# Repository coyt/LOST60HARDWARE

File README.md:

# LOST60HARDWARE
Hardware design files for LOST60 Bluetooth Mechanical Keyboard

#### LOST60 PCB Version 2.0 (SPRING 2020)

#### LOST60 PCB Version 1.0 (FALL 2019)

*The Ultimate Hackable Bluetooth Mechanical Keyboard*

#### Overview

Hardware design files for the LOST60 Bluetooth 60% Mechanical Keyboard PCB. The PCB utilizes a Nordic Semiconductor [nrf52840 bluetooth SoC](https://www.nordicsemi.com/?sc_itemid=%7B2DC10BA5-A76E-40F8-836E-E2FC65803A71%7D) (Rigado BMD-340 module) as the sole processor.

#### PCB Artwork

#### 3D Modeling

#### Version 2.0 System Diagram

#### Hardware Features
* 60% Mechanical Keyboard design based on GH60 Layout
* USBC connector
* Bluetooth 5.0 support
* Full RGB underlighting with "neopixels"
* Independently addressable single color key backlingting
* Qi wireless charging
* Advanced battery charging and management circuitry
* Rotary encoder and TWO speakers for Synthesizer features (under development)
* Several expansion ports (QUIIC, GROVE, CUSTOM)

#### Planned Hardware Updates

- [x] Add coulomb counting IC / improve voltage and power measurement   (Complete in V2.0)
- [ ] Improve backlighting LED brightness 
- [x] Extend USB C connector out a bit                                  (Complete in V2.0)
- [x] Fix underlighting load switch fly wire                            (Complete in V2.0)
- [x] Fix LiPo charger ground pour problem & improve charge rate        (Complete in V2.0)
- [x] Remove onboard Lithium protection IC                              (Complete in V2.0)
- [ ] Add physical power switch connection point 
- [ ] Change wiring so I/O emulates Feather nrf52840 board
- [x] Add QSPI memory chip                                              (Complete in V2.0)

#### Development Setup

This design was created using Eagle PCB for schematic capture and PCB layout and routing. Fusion 360 was used to generate CAD model of board before manufacture.

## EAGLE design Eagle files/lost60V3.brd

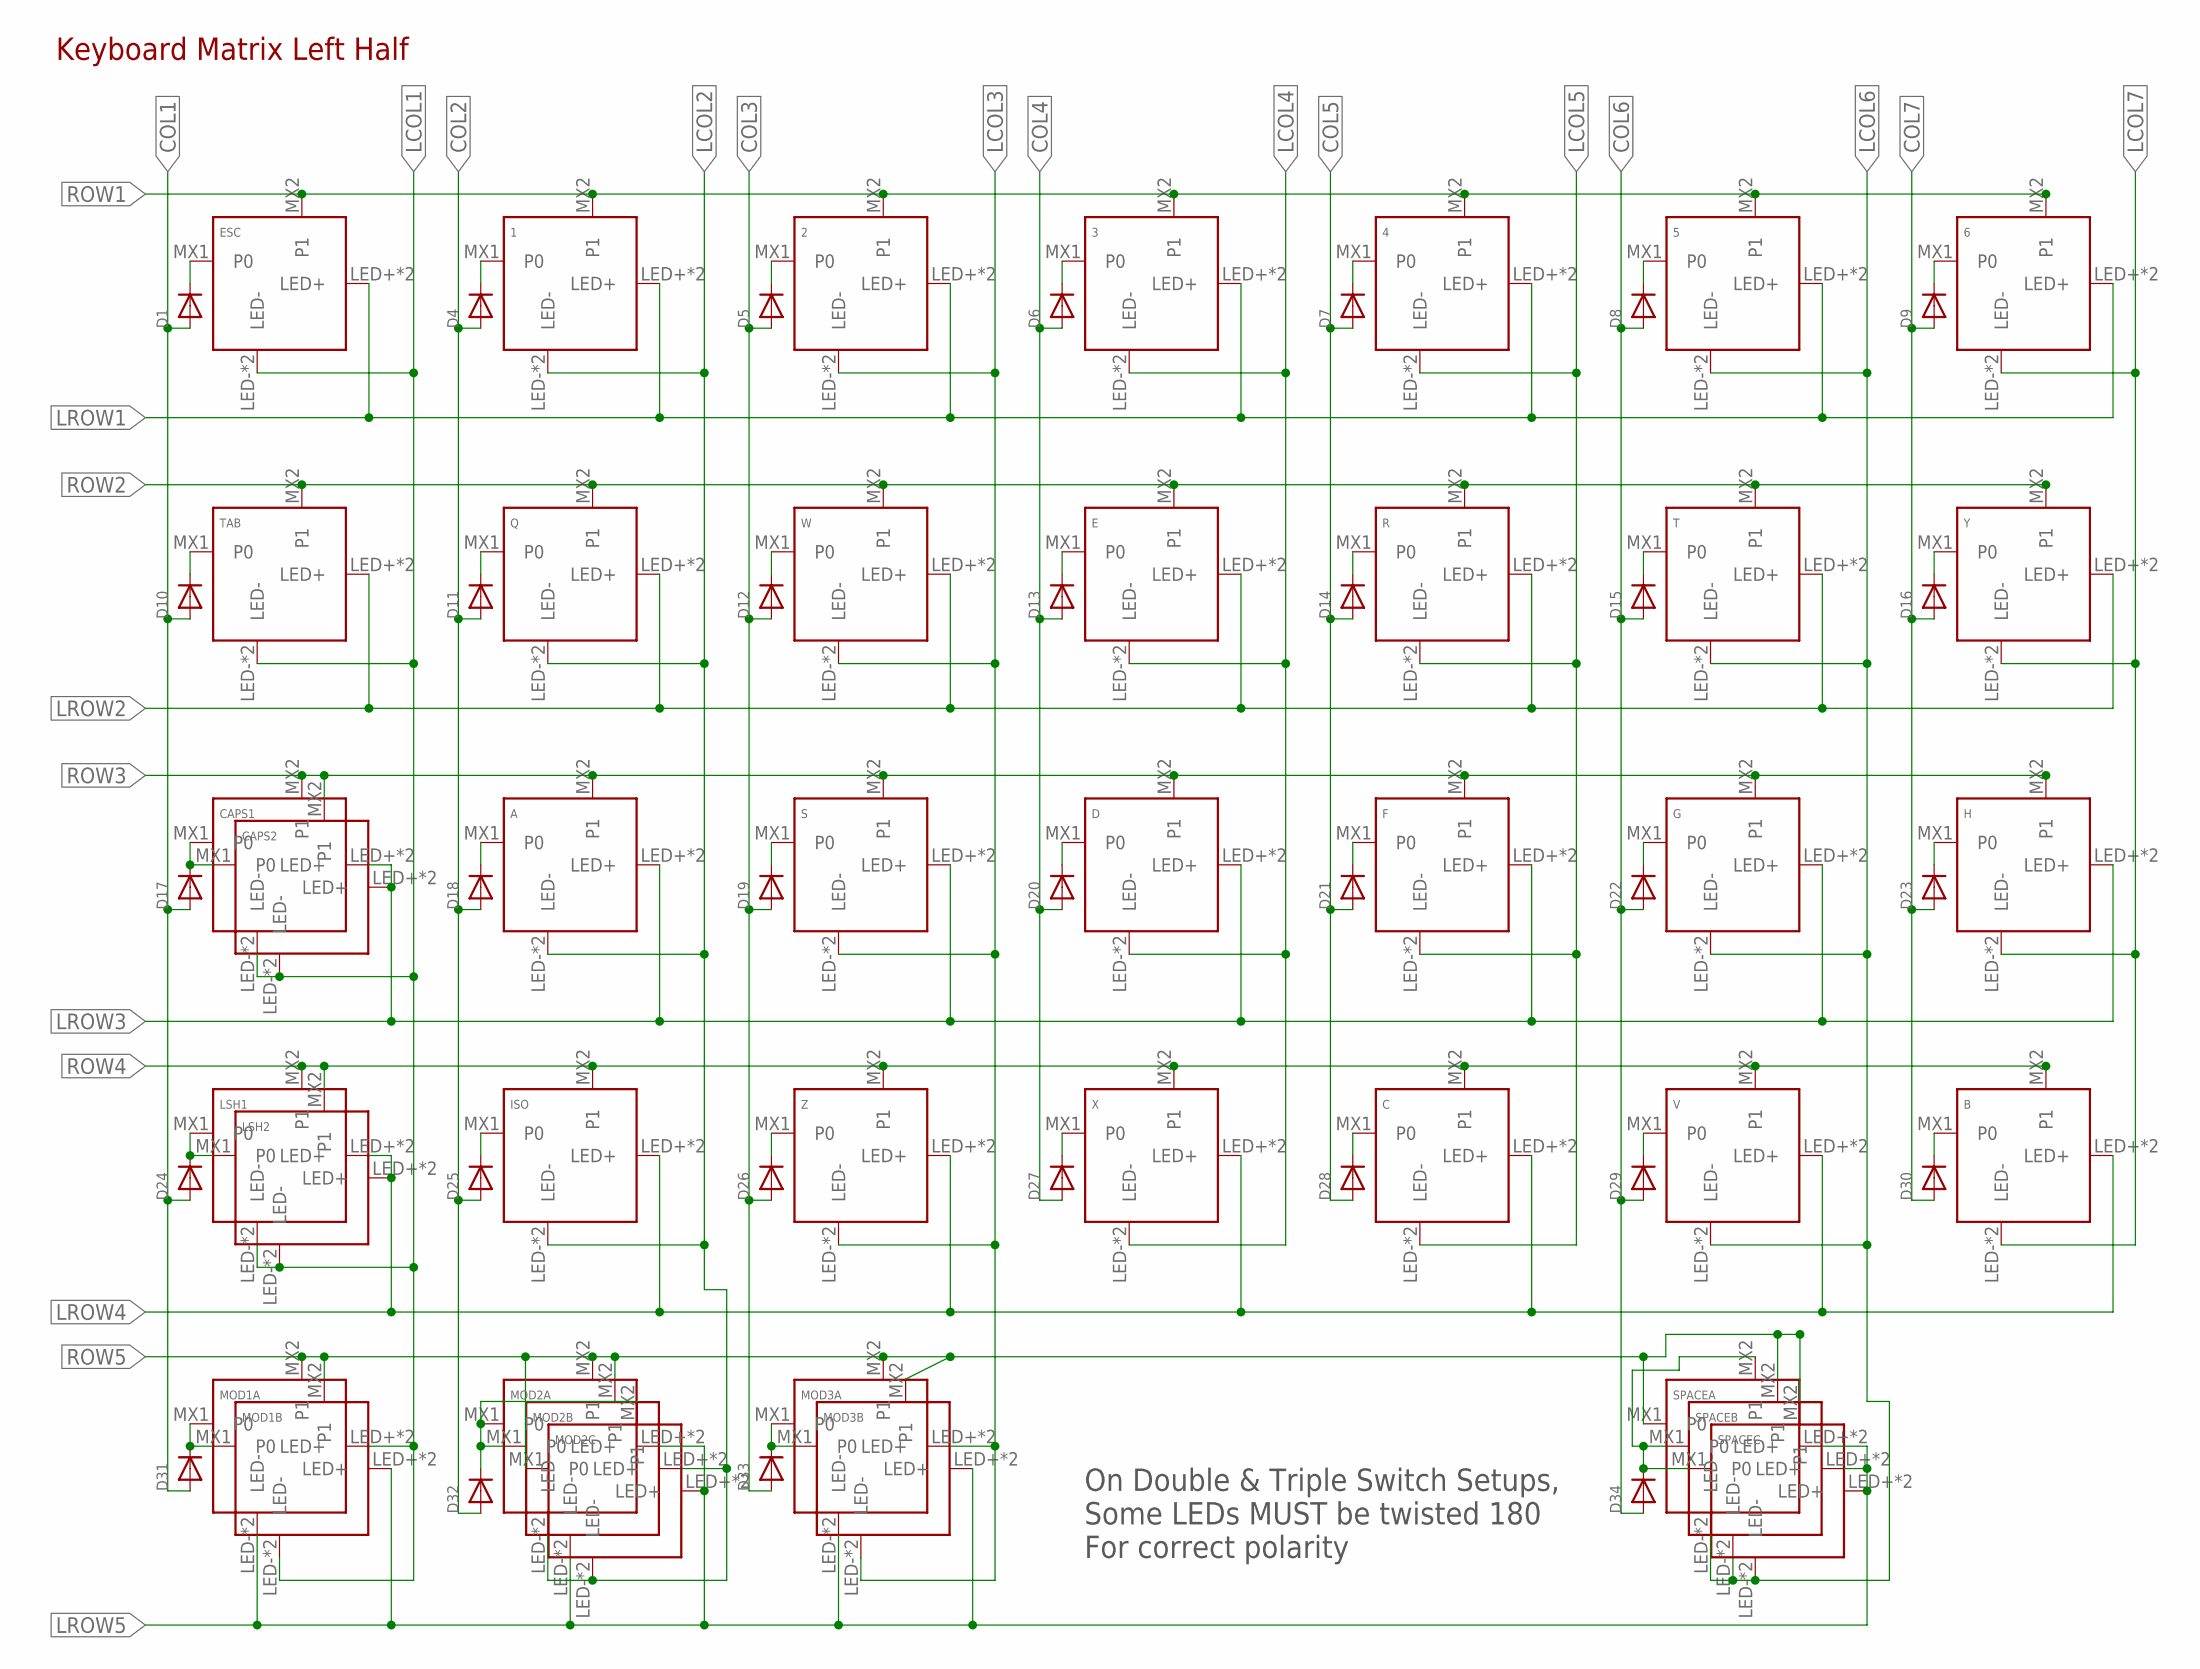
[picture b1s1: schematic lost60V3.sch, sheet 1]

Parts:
1, 2, 3, 4, 5, 6: KEYSWITCH-THTSMDLED-MX-1U-THTSMDLED; MX-1U-THTSMDLED
A: KEYSWITCH-THTSMDLED-MX-1U-THTSMDLED; MX-1U-THTSMDLED
B: KEYSWITCH-THTSMDLED-MX-1U-THTSMDLED; MX-1U-THTSMDLED
C: KEYSWITCH-THTSMDLED-MX-1U-THTSMDLED; MX-1U-THTSMDLED
CAPS1, CAPS2: KEYSWITCH-THTSMDLED-MX-1U-THTSMDLED; MX-1U-THTSMDLED
D: KEYSWITCH-THTSMDLED-MX-1U-THTSMDLED; MX-1U-THTSMDLED
D1, D4, D5, D6, D7, D8, D9, D10, D11, D12, D13, D14, D15, D16, D17, D18, D19, D20, D21, D22, D23, D24, D25, D26, D27, D28, D29, D30, D31, D32, D33, D34: DIODESOD-523; SOD-523
E: KEYSWITCH-THTSMDLED-MX-1U-THTSMDLED; MX-1U-THTSMDLED
ESC: KEYSWITCH-THTSMDLED-MX-1U-THTSMDLED; MX-1U-THTSMDLED
F: KEYSWITCH-THTSMDLED-MX-1U-THTSMDLED; MX-1U-THTSMDLED
G: KEYSWITCH-THTSMDLED-MX-1U-THTSMDLED; MX-1U-THTSMDLED
H: KEYSWITCH-THTSMDLED-MX-1U-THTSMDLED; MX-1U-THTSMDLED
ISO: KEYSWITCH-THTSMDLED-MX-1U-THTSMDLED; MX-1U-THTSMDLED
LSH1: KEYSWITCH-THTSMDLED-MX-1U-THTSMDLED; MX-1U-THTSMDLED
LSH2: KEYSWITCH-THTSMDLED-MX-2U-THTSMDLED; MX-2U-THTSMDLED
MOD1A, MOD1B, MOD2A, MOD2B, MOD2C, MOD3A, MOD3B: KEYSWITCH-THTSMDLED-MX-1U-THTSMDLED; MX-1U-THTSMDLED
Q: KEYSWITCH-THTSMDLED-MX-1U-THTSMDLED; MX-1U-THTSMDLED
R: KEYSWITCH-THTSMDLED-MX-1U-THTSMDLED; MX-1U-THTSMDLED
S: KEYSWITCH-THTSMDLED-MX-1U-THTSMDLED; MX-1U-THTSMDLED
SPACEA: KEYSWITCH-THTSMDLED-MX-6.25U-THTSMDLED-FLIPPED; MX-6.25U-THTSMDLED-FLIPPED
SPACEB: KEYSWITCH-THTSMDLED-MX-7U-THTSMDLED-FLIPPED; MX-7U-THTSMDLED-FLIPPED
SPACEC: KEYSWITCH-THTSMDLED-MX-7U-THTSMDLED-FLIPPED; MX-7U-THTSMDLED-FLIPPED
T: KEYSWITCH-THTSMDLED-MX-1U-THTSMDLED; MX-1U-THTSMDLED
TAB: KEYSWITCH-THTSMDLED-MX-1U-THTSMDLED; MX-1U-THTSMDLED
V: KEYSWITCH-THTSMDLED-MX-1U-THTSMDLED; MX-1U-THTSMDLED
W: KEYSWITCH-THTSMDLED-MX-1U-THTSMDLED; MX-1U-THTSMDLED
X: KEYSWITCH-THTSMDLED-MX-1U-THTSMDLED; MX-1U-THTSMDLED
Y: KEYSWITCH-THTSMDLED-MX-1U-THTSMDLED; MX-1U-THTSMDLED
Z: KEYSWITCH-THTSMDLED-MX-1U-THTSMDLED; MX-1U-THTSMDLED

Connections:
COL1: D1.A, D10.A, D17.A, D24.A, D31.A; also elsewhere on the board
COL2: D4.A, D11.A, D18.A, D25.A, D32.A; also elsewhere on the board
COL3: D5.A, D12.A, D19.A, D26.A, D33.A; also elsewhere on the board
COL4: D6.A, D13.A, D20.A, D27.A; also elsewhere on the board
COL5: D7.A, D14.A, D21.A, D28.A; also elsewhere on the board
COL6: D8.A, D15.A, D22.A, D29.A, D34.A; also elsewhere on the board
COL7: D9.A, D16.A, D23.A, D30.A; also elsewhere on the board
LCOL1: CAPS1.LED-, CAPS1.SMDLED- (LED-), CAPS2.LED-, CAPS2.SMDLED- (LED-), ESC.LED-, ESC.SMDLED- (LED-), LSH1.LED-, LSH1.SMDLED- (LED-), LSH2.LED-, LSH2.SMDLED- (LED-), MOD1A.LED+, MOD1A.SMDLED+ (LED+), MOD1B.LED-, MOD1B.SMDLED- (LED-), TAB.LED-, TAB.SMDLED- (LED-); also elsewhere on the board
LCOL2: 1.LED-, 1.SMDLED- (LED-), A.LED-, A.SMDLED- (LED-), ISO.LED-, ISO.SMDLED- (LED-), MOD2A.LED-, MOD2A.SMDLED- (LED-), MOD2B.LED+, MOD2B.SMDLED+ (LED+), MOD2C.LED-, MOD2C.SMDLED- (LED-), Q.LED-, Q.SMDLED- (LED-); also elsewhere on the board
LCOL3: 2.LED-, 2.SMDLED- (LED-), MOD3A.LED+, MOD3A.SMDLED+ (LED+), MOD3B.LED-, MOD3B.SMDLED- (LED-), S.LED-, S.SMDLED- (LED-), W.LED-, W.SMDLED- (LED-), Z.LED-, Z.SMDLED- (LED-); also elsewhere on the board
LCOL4: 3.LED-, 3.SMDLED- (LED-), D.LED-, D.SMDLED- (LED-), E.LED-, E.SMDLED- (LED-), X.LED-, X.SMDLED- (LED-); also elsewhere on the board
LCOL5: 4.LED-, 4.SMDLED- (LED-), C.LED-, C.SMDLED- (LED-), F.LED-, F.SMDLED- (LED-), R.LED-, R.SMDLED- (LED-); also elsewhere on the board
LCOL6: 5.LED-, 5.SMDLED- (LED-), G.LED-, G.SMDLED- (LED-), SPACEA.LED-, SPACEA.SMDLED- (LED-), SPACEB.LED-, SPACEB.SMDLED- (LED-), SPACEC.LED-, SPACEC.SMDLED- (LED-), T.LED-, T.SMDLED- (LED-), V.LED-, V.SMDLED- (LED-); also elsewhere on the board
LCOL7: 6.LED-, 6.SMDLED- (LED-), B.LED-, B.SMDLED- (LED-), H.LED-, H.SMDLED- (LED-), Y.LED-, Y.SMDLED- (LED-); also elsewhere on the board
LROW1: 1.LED+, 1.SMDLED+ (LED+), 2.LED+, 2.SMDLED+ (LED+), 3.LED+, 3.SMDLED+ (LED+), 4.LED+, 4.SMDLED+ (LED+), 5.LED+, 5.SMDLED+ (LED+), 6.LED+, 6.SMDLED+ (LED+), ESC.LED+, ESC.SMDLED+ (LED+); also elsewhere on the board
LROW2: E.LED+, E.SMDLED+ (LED+), Q.LED+, Q.SMDLED+ (LED+), R.LED+, R.SMDLED+ (LED+), T.LED+, T.SMDLED+ (LED+), TAB.LED+, TAB.SMDLED+ (LED+), W.LED+, W.SMDLED+ (LED+), Y.LED+, Y.SMDLED+ (LED+); also elsewhere on the board
LROW3: A.LED+, A.SMDLED+ (LED+), CAPS1.LED+, CAPS1.SMDLED+ (LED+), CAPS2.LED+, CAPS2.SMDLED+ (LED+), D.LED+, D.SMDLED+ (LED+), F.LED+, F.SMDLED+ (LED+), G.LED+, G.SMDLED+ (LED+), H.LED+, H.SMDLED+ (LED+), S.LED+, S.SMDLED+ (LED+); also elsewhere on the board
LROW4: B.LED+, B.SMDLED+ (LED+), C.LED+, C.SMDLED+ (LED+), ISO.LED+, ISO.SMDLED+ (LED+), LSH1.LED+, LSH1.SMDLED+ (LED+), LSH2.LED+, LSH2.SMDLED+ (LED+), V.LED+, V.SMDLED+ (LED+), X.LED+, X.SMDLED+ (LED+), Z.LED+, Z.SMDLED+ (LED+); also elsewhere on the board
LROW5: MOD1A.LED-, MOD1A.SMDLED- (LED-), MOD1B.LED+, MOD1B.SMDLED+ (LED+), MOD2A.LED+, MOD2A.SMDLED+ (LED+), MOD2B.LED-, MOD2B.SMDLED- (LED-), MOD2C.LED+, MOD2C.SMDLED+ (LED+), MOD3A.LED-, MOD3A.SMDLED- (LED-), MOD3B.LED+, MOD3B.SMDLED+ (LED+), SPACEA.LED+, SPACEA.SMDLED+ (LED+), SPACEB.LED+, SPACEB.SMDLED+ (LED+), SPACEC.LED+, SPACEC.SMDLED+ (LED+); also elsewhere on the board
unnamed: D1.K (C), ESC.MX1 (P0)
unnamed: 1.MX1 (P0), D4.K (C)
unnamed: 2.MX1 (P0), D5.K (C)
unnamed: 3.MX1 (P0), D6.K (C)
unnamed: 4.MX1 (P0), D7.K (C)
unnamed: 5.MX1 (P0), D8.K (C)
unnamed: 6.MX1 (P0), D9.K (C)
unnamed: D10.K (C), TAB.MX1 (P0)
unnamed: D11.K (C), Q.MX1 (P0)
unnamed: D12.K (C), W.MX1 (P0)
unnamed: D13.K (C), E.MX1 (P0)
unnamed: D14.K (C), R.MX1 (P0)
unnamed: D15.K (C), T.MX1 (P0)
unnamed: D16.K (C), Y.MX1 (P0)
unnamed: D34.K (C), SPACEA.MX2 (P1), SPACEB.MX1 (P0), SPACEC.MX1 (P0)
unnamed: CAPS1.MX1 (P0), CAPS2.MX1 (P0), D17.K (C)
unnamed: A.MX1 (P0), D18.K (C)
unnamed: D19.K (C), S.MX1 (P0)
unnamed: D.MX1 (P0), D20.K (C)
unnamed: D21.K (C), F.MX1 (P0)
unnamed: D23.K (C), H.MX1 (P0)
unnamed: D24.K (C), LSH1.MX1 (P0), LSH2.MX1 (P0)
unnamed: D25.K (C), ISO.MX1 (P0)
unnamed: D26.K (C), Z.MX1 (P0)
unnamed: D27.K (C), X.MX1 (P0)
unnamed: C.MX1 (P0), D28.K (C)
unnamed: D29.K (C), V.MX1 (P0)
unnamed: B.MX1 (P0), D30.K (C)
unnamed: D31.K (C), MOD1A.MX1 (P0), MOD1B.MX1 (P0)
unnamed: D32.K (C), MOD2A.MX1 (P0), MOD2B.MX1 (P0), MOD2C.MX2 (P1)
unnamed: D33.K (C), MOD3A.MX1 (P0), MOD3B.MX1 (P0)
unnamed: D22.K (C), G.MX1 (P0)
ROW1: 1.MX2 (P1), 2.MX2 (P1), 3.MX2 (P1), 4.MX2 (P1), 5.MX2 (P1), 6.MX2 (P1), ESC.MX2 (P1); also elsewhere on the board
ROW2: E.MX2 (P1), Q.MX2 (P1), R.MX2 (P1), T.MX2 (P1), TAB.MX2 (P1), W.MX2 (P1), Y.MX2 (P1); also elsewhere on the board
ROW3: A.MX2 (P1), CAPS1.MX2 (P1), CAPS2.MX2 (P1), D.MX2 (P1), F.MX2 (P1), G.MX2 (P1), H.MX2 (P1), S.MX2 (P1); also elsewhere on the board
ROW4: B.MX2 (P1), C.MX2 (P1), ISO.MX2 (P1), LSH1.MX2 (P1), LSH2.MX2 (P1), V.MX2 (P1), X.MX2 (P1), Z.MX2 (P1); also elsewhere on the board
ROW5: MOD1A.MX2 (P1), MOD1B.MX2 (P1), MOD2A.MX2 (P1), MOD2B.MX2 (P1), MOD2C.MX1 (P0), MOD3A.MX2 (P1), MOD3B.MX2 (P1), SPACEA.MX1 (P0), SPACEB.MX2 (P1), SPACEC.MX2 (P1); also elsewhere on the board

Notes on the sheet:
Keyboard Matrix Left Half
On Double & Triple Switch Setups, Some LEDs MUST be twisted 180 For correct polarity

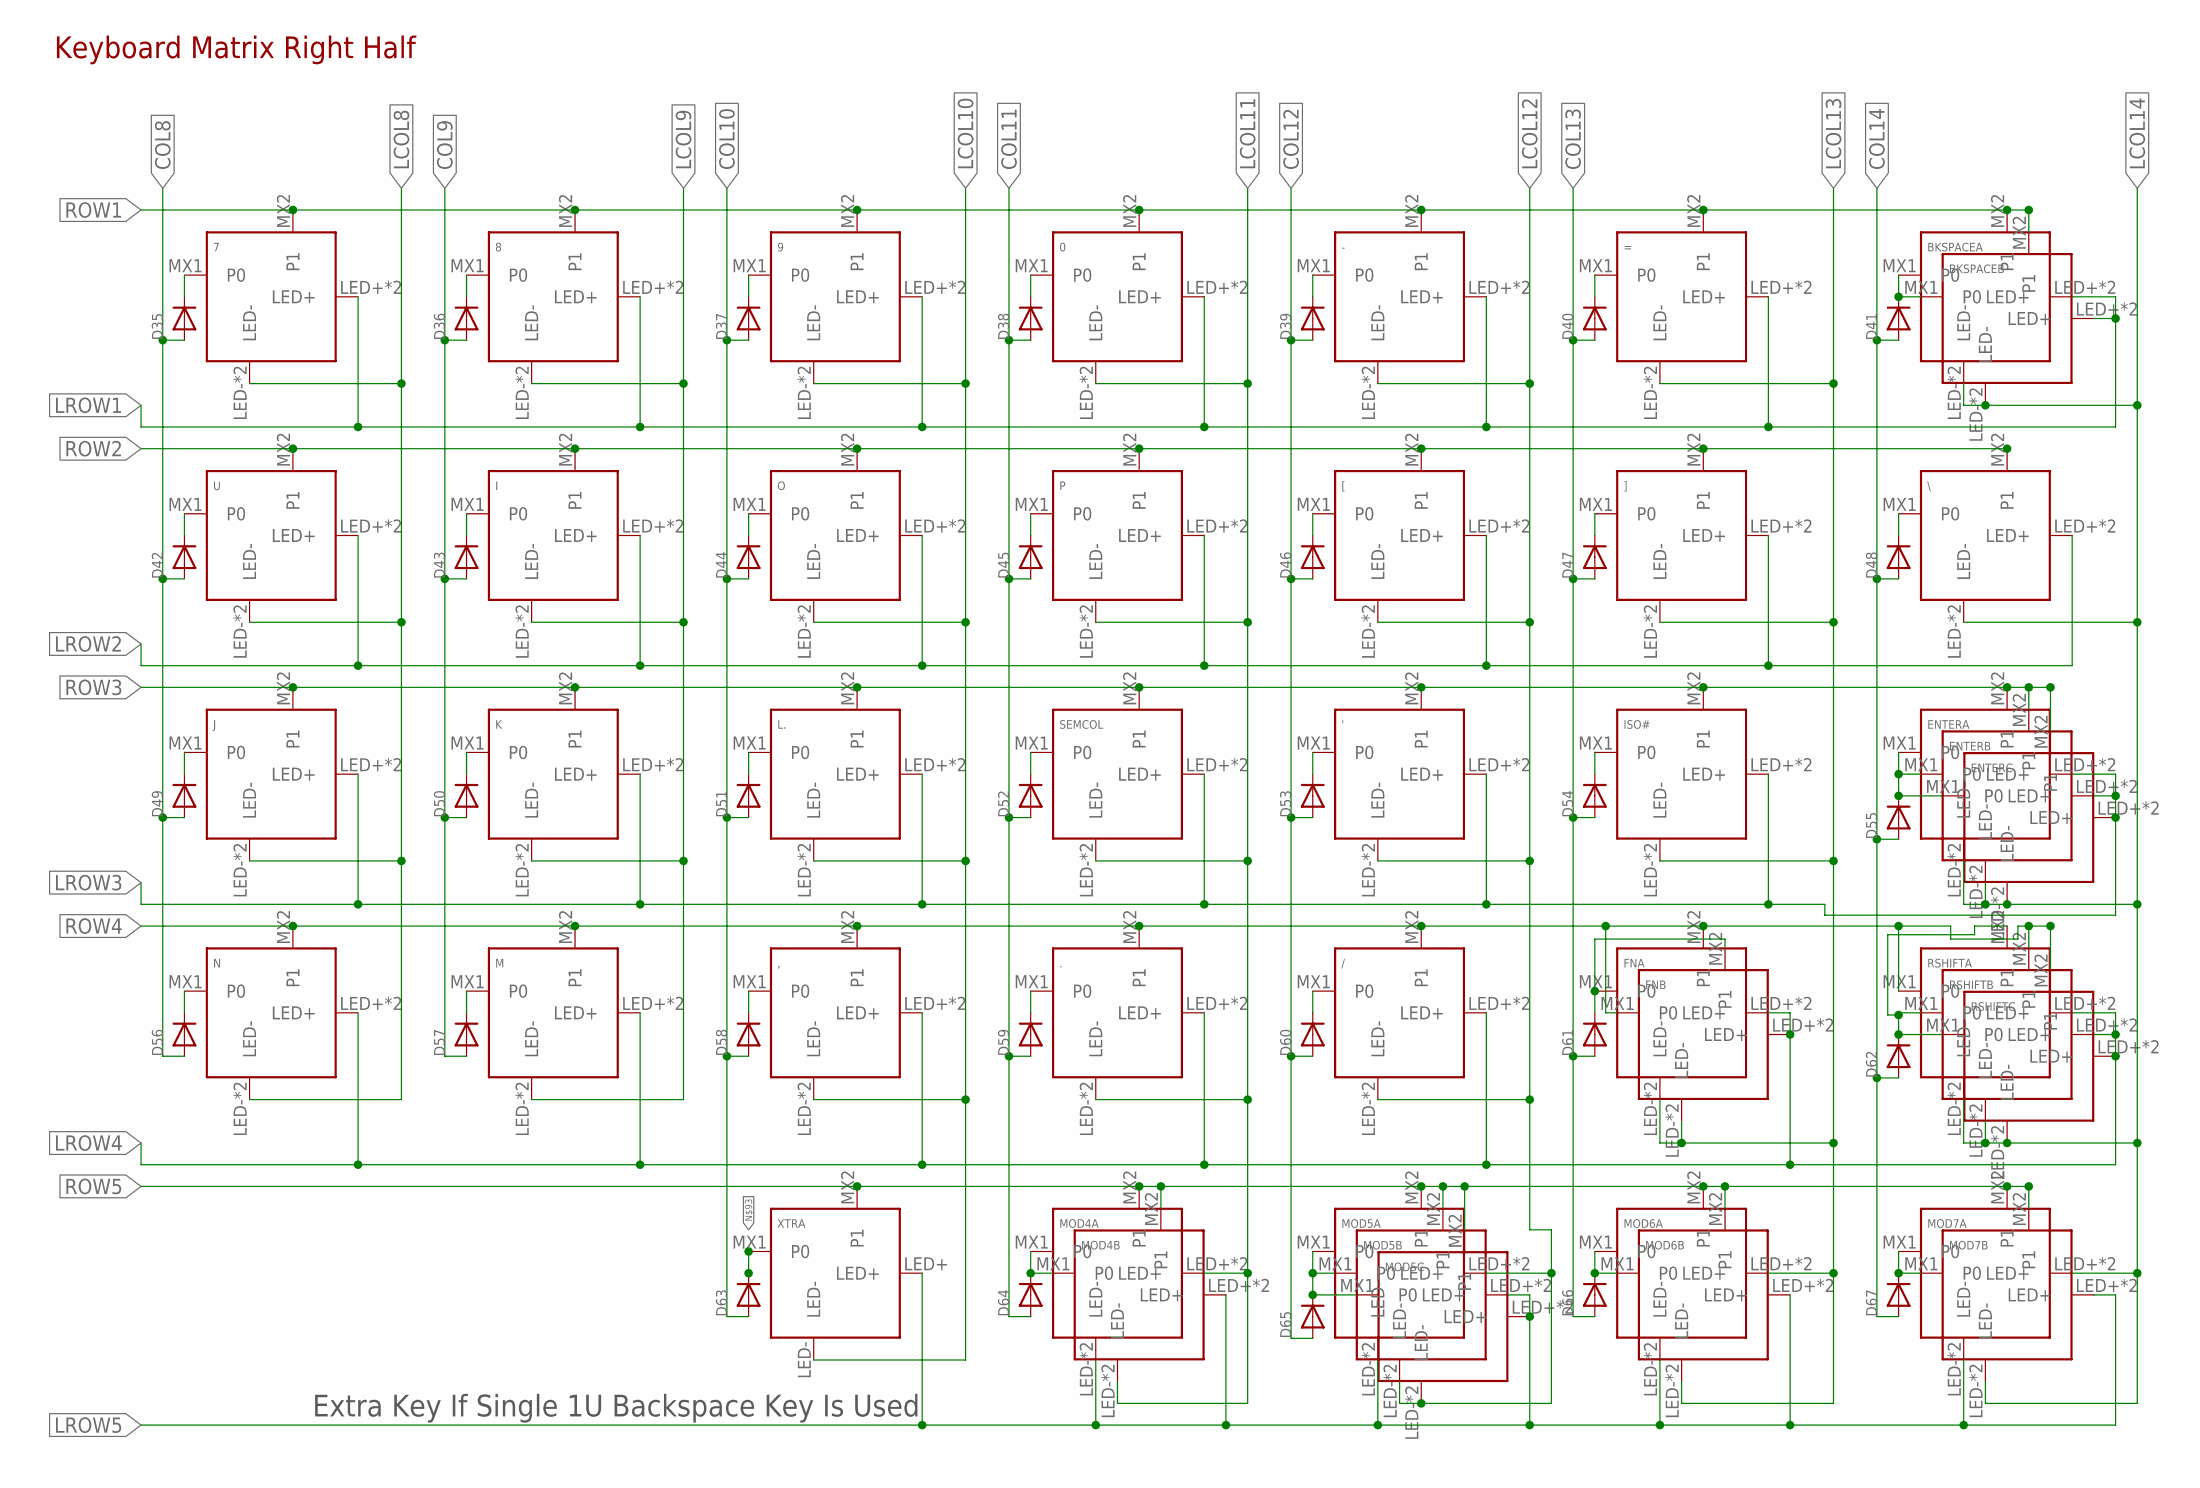
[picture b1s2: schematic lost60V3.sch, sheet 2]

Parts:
0, 7, 8, 9, .: KEYSWITCH-THTSMDLED-MX-1U-THTSMDLED; MX-1U-THTSMDLED
': KEYSWITCH-THTSMDLED-MX-1U-THTSMDLED; MX-1U-THTSMDLED
,: KEYSWITCH-THTSMDLED-MX-1U-THTSMDLED; MX-1U-THTSMDLED
-: KEYSWITCH-THTSMDLED-MX-1U-THTSMDLED; MX-1U-THTSMDLED
/: KEYSWITCH-THTSMDLED-MX-1U-THTSMDLED; MX-1U-THTSMDLED
=: KEYSWITCH-THTSMDLED-MX-1U-THTSMDLED; MX-1U-THTSMDLED
BKSPACEA: KEYSWITCH-THTSMDLED-MX-1U-THTSMDLED; MX-1U-THTSMDLED
BKSPACEB: KEYSWITCH-THTSMDLED-MX-2U-THTSMDLED; MX-2U-THTSMDLED
D35, D36, D37, D38, D39, D40, D41, D42, D43, D44, D45, D46, D47, D48, D49, D50, D51, D52, D53, D54, D55, D56, D57, D58, D59, D60, D61, D62, D63, D64, D65, D66, D67: DIODESOD-523; SOD-523
ENTERA: KEYSWITCH-THTSMDLED-MX-1U-THTSMDLED; MX-1U-THTSMDLED
ENTERB: KEYSWITCH-THTSMDLED-MX-2U-THTSMDLED; MX-2U-THTSMDLED
ENTERC: KEYSWITCH-THTSMDLED-MX-2U-THTSMDLED; MX-2U-THTSMDLED
FNA: KEYSWITCH-THTSMDLED-MX-1U-THTSMDLED; MX-1U-THTSMDLED
FNB: KEYSWITCH-THTSMDLED-MX-1U-THTSMDLED; MX-1U-THTSMDLED
I: KEYSWITCH-THTSMDLED-MX-1U-THTSMDLED; MX-1U-THTSMDLED
ISO#: KEYSWITCH-THTSMDLED-MX-1U-THTSMDLED; MX-1U-THTSMDLED
J: KEYSWITCH-THTSMDLED-MX-1U-THTSMDLED; MX-1U-THTSMDLED
K: KEYSWITCH-THTSMDLED-MX-1U-THTSMDLED; MX-1U-THTSMDLED
L.: KEYSWITCH-THTSMDLED-MX-1U-THTSMDLED; MX-1U-THTSMDLED
M: KEYSWITCH-THTSMDLED-MX-1U-THTSMDLED; MX-1U-THTSMDLED
MOD4A, MOD4B, MOD5A, MOD5B, MOD5C, MOD6A, MOD6B, MOD7A, MOD7B: KEYSWITCH-THTSMDLED-MX-1U-THTSMDLED; MX-1U-THTSMDLED
N: KEYSWITCH-THTSMDLED-MX-1U-THTSMDLED; MX-1U-THTSMDLED
O: KEYSWITCH-THTSMDLED-MX-1U-THTSMDLED; MX-1U-THTSMDLED
P: KEYSWITCH-THTSMDLED-MX-1U-THTSMDLED; MX-1U-THTSMDLED
RSHIFTA: KEYSWITCH-THTSMDLED-MX-1U-THTSMDLED; MX-1U-THTSMDLED
RSHIFTB: KEYSWITCH-THTSMDLED-MX-1U-THTSMDLED; MX-1U-THTSMDLED
RSHIFTC: KEYSWITCH-THTSMDLED-MX-2U-THTSMDLED; MX-2U-THTSMDLED
SEMCOL: KEYSWITCH-THTSMDLED-MX-1U-THTSMDLED; MX-1U-THTSMDLED
U: KEYSWITCH-THTSMDLED-MX-1U-THTSMDLED; MX-1U-THTSMDLED
XTRA: KEYSWITCH-THTSMDLED-MOD1; MX-1U-THTSMDLED-MOD1
[: KEYSWITCH-THTSMDLED-MX-1U-THTSMDLED; MX-1U-THTSMDLED
\: KEYSWITCH-THTSMDLED-MX-1U-THTSMDLED; MX-1U-THTSMDLED
]: KEYSWITCH-THTSMDLED-MX-1U-THTSMDLED; MX-1U-THTSMDLED

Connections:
COL8: D35.A, D42.A, D49.A, D56.A; also elsewhere on the board
COL9: D36.A, D43.A, D50.A, D57.A; also elsewhere on the board
COL10: D37.A, D44.A, D51.A, D58.A, D63.A; also elsewhere on the board
COL11: D38.A, D45.A, D52.A, D59.A, D64.A; also elsewhere on the board
COL12: D39.A, D46.A, D53.A, D60.A, D65.A; also elsewhere on the board
COL13: D40.A, D47.A, D54.A, D61.A, D66.A; also elsewhere on the board
COL14: D41.A, D48.A, D55.A, D62.A, D67.A; also elsewhere on the board
LCOL8: 7.LED-, 7.SMDLED- (LED-), J.LED-, J.SMDLED- (LED-), N.LED-, N.SMDLED- (LED-), U.LED-, U.SMDLED- (LED-); also elsewhere on the board
LCOL9: 8.LED-, 8.SMDLED- (LED-), I.LED-, I.SMDLED- (LED-), K.LED-, K.SMDLED- (LED-), M.LED-, M.SMDLED- (LED-); also elsewhere on the board
LCOL10: 9.LED-, 9.SMDLED- (LED-), ,.LED-, ,.SMDLED- (LED-), L..LED-, L..SMDLED- (LED-), O.LED-, O.SMDLED- (LED-), XTRA.LED-; also elsewhere on the board
LCOL11: 0.LED-, 0.SMDLED- (LED-), ..LED-, ..SMDLED- (LED-), MOD4A.LED+, MOD4A.SMDLED+ (LED+), MOD4B.LED-, MOD4B.SMDLED- (LED-), P.LED-, P.SMDLED- (LED-), SEMCOL.LED-, SEMCOL.SMDLED- (LED-); also elsewhere on the board
LCOL12: '.LED-, '.SMDLED- (LED-), -.LED-, -.SMDLED- (LED-), /.LED-, /.SMDLED- (LED-), MOD5A.LED+, MOD5A.SMDLED+ (LED+), MOD5B.LED-, MOD5B.SMDLED- (LED-), MOD5C.LED-, MOD5C.SMDLED- (LED-), [.LED-, [.SMDLED- (LED-); also elsewhere on the board
LCOL13: =.LED-, =.SMDLED- (LED-), FNA.LED-, FNA.SMDLED- (LED-), FNB.LED-, FNB.SMDLED- (LED-), ISO#.LED-, ISO#.SMDLED- (LED-), MOD6A.LED+, MOD6A.SMDLED+ (LED+), MOD6B.LED-, MOD6B.SMDLED- (LED-), ].LED-, ].SMDLED- (LED-); also elsewhere on the board
LCOL14: BKSPACEA.LED-, BKSPACEA.SMDLED- (LED-), BKSPACEB.LED-, BKSPACEB.SMDLED- (LED-), ENTERA.LED-, ENTERA.SMDLED- (LED-), ENTERB.LED-, ENTERB.SMDLED- (LED-), ENTERC.LED-, ENTERC.SMDLED- (LED-), MOD7A.LED+, MOD7A.SMDLED+ (LED+), MOD7B.LED-, MOD7B.SMDLED- (LED-), RSHIFTA.LED-, RSHIFTA.SMDLED- (LED-), RSHIFTB.LED-, RSHIFTB.SMDLED- (LED-), RSHIFTC.LED-, RSHIFTC.SMDLED- (LED-), \.LED-, \.SMDLED- (LED-); also elsewhere on the board
LROW1: 0.LED+, 0.SMDLED+ (LED+), 7.LED+, 7.SMDLED+ (LED+), 8.LED+, 8.SMDLED+ (LED+), 9.LED+, 9.SMDLED+ (LED+), -.LED+, -.SMDLED+ (LED+), =.LED+, =.SMDLED+ (LED+), BKSPACEA.LED+, BKSPACEA.SMDLED+ (LED+), BKSPACEB.LED+, BKSPACEB.SMDLED+ (LED+); also elsewhere on the board
LROW2: I.LED+, I.SMDLED+ (LED+), O.LED+, O.SMDLED+ (LED+), P.LED+, P.SMDLED+ (LED+), U.LED+, U.SMDLED+ (LED+), [.LED+, [.SMDLED+ (LED+), \.LED+, \.SMDLED+ (LED+), ].LED+, ].SMDLED+ (LED+); also elsewhere on the board
LROW3: '.LED+, '.SMDLED+ (LED+), ENTERA.LED+, ENTERA.SMDLED+ (LED+), ENTERB.LED+, ENTERB.SMDLED+ (LED+), ENTERC.LED+, ENTERC.SMDLED+ (LED+), ISO#.LED+, ISO#.SMDLED+ (LED+), J.LED+, J.SMDLED+ (LED+), K.LED+, K.SMDLED+ (LED+), L..LED+, L..SMDLED+ (LED+), SEMCOL.LED+, SEMCOL.SMDLED+ (LED+); also elsewhere on the board
LROW4: ,.LED+, ,.SMDLED+ (LED+), ..LED+, ..SMDLED+ (LED+), /.LED+, /.SMDLED+ (LED+), FNA.LED+, FNA.SMDLED+ (LED+), FNB.LED+, FNB.SMDLED+ (LED+), M.LED+, M.SMDLED+ (LED+), N.LED+, N.SMDLED+ (LED+), RSHIFTA.LED+, RSHIFTA.SMDLED+ (LED+), RSHIFTB.LED+, RSHIFTB.SMDLED+ (LED+), RSHIFTC.LED+, RSHIFTC.SMDLED+ (LED+); also elsewhere on the board
LROW5: MOD4A.LED-, MOD4A.SMDLED- (LED-), MOD4B.LED+, MOD4B.SMDLED+ (LED+), MOD5A.LED-, MOD5A.SMDLED- (LED-), MOD5B.LED+, MOD5B.SMDLED+ (LED+), MOD5C.LED+, MOD5C.SMDLED+ (LED+), MOD6A.LED-, MOD6A.SMDLED- (LED-), MOD6B.LED+, MOD6B.SMDLED+ (LED+), MOD7A.LED-, MOD7A.SMDLED- (LED-), MOD7B.LED+, MOD7B.SMDLED+ (LED+), XTRA.LED+; also elsewhere on the board
unnamed: 7.MX1 (P0), D35.K (C)
unnamed: D62.K (C), RSHIFTA.MX2 (P1), RSHIFTB.MX1 (P0), RSHIFTC.MX1 (P0)
unnamed: 8.MX1 (P0), D36.K (C)
unnamed: 9.MX1 (P0), D37.K (C)
unnamed: 0.MX1 (P0), D38.K (C)
unnamed: -.MX1 (P0), D39.K (C)
unnamed: =.MX1 (P0), D40.K (C)
unnamed: BKSPACEA.MX1 (P0), BKSPACEB.MX1 (P0), D41.K (C)
unnamed: D42.K (C), U.MX1 (P0)
unnamed: D43.K (C), I.MX1 (P0)
unnamed: D44.K (C), O.MX1 (P0)
unnamed: D45.K (C), P.MX1 (P0)
unnamed: D46.K (C), [.MX1 (P0)
unnamed: D47.K (C), ].MX1 (P0)
unnamed: D48.K (C), \.MX1 (P0)
unnamed: D49.K (C), J.MX1 (P0)
unnamed: D50.K (C), K.MX1 (P0)
unnamed: D51.K (C), L..MX1 (P0)
unnamed: D52.K (C), SEMCOL.MX1 (P0)
unnamed: '.MX1 (P0), D53.K (C)
unnamed: D54.K (C), ISO#.MX1 (P0)
unnamed: D55.K (C), ENTERA.MX1 (P0), ENTERB.MX1 (P0), ENTERC.MX1 (P0)
unnamed: D56.K (C), N.MX1 (P0)
unnamed: D57.K (C), M.MX1 (P0)
unnamed: ,.MX1 (P0), D58.K (C)
unnamed: ..MX1 (P0), D59.K (C)
unnamed: /.MX1 (P0), D60.K (C)
unnamed: D61.K (C), FNA.MX1 (P0), FNB.MX2 (P1)
unnamed 147: D63.K (C), XTRA.MX1 (P0); also elsewhere on the board
unnamed: D64.K (C), MOD4A.MX1 (P0), MOD4B.MX1 (P0)
unnamed: D65.K (C), MOD5A.MX1 (P0), MOD5B.MX1 (P0), MOD5C.MX1 (P0)
unnamed: D66.K (C), MOD6A.MX1 (P0), MOD6B.MX1 (P0)
unnamed: D67.K (C), MOD7A.MX1 (P0), MOD7B.MX1 (P0)
ROW1: 0.MX2 (P1), 7.MX2 (P1), 8.MX2 (P1), 9.MX2 (P1), -.MX2 (P1), =.MX2 (P1), BKSPACEA.MX2 (P1), BKSPACEB.MX2 (P1); also elsewhere on the board
ROW2: I.MX2 (P1), O.MX2 (P1), P.MX2 (P1), U.MX2 (P1), [.MX2 (P1), \.MX2 (P1), ].MX2 (P1); also elsewhere on the board
ROW3: '.MX2 (P1), ENTERA.MX2 (P1), ENTERB.MX2 (P1), ENTERC.MX2 (P1), ISO#.MX2 (P1), J.MX2 (P1), K.MX2 (P1), L..MX2 (P1), SEMCOL.MX2 (P1); also elsewhere on the board
ROW4: ,.MX2 (P1), ..MX2 (P1), /.MX2 (P1), FNA.MX2 (P1), FNB.MX1 (P0), M.MX2 (P1), N.MX2 (P1), RSHIFTA.MX1 (P0), RSHIFTB.MX2 (P1), RSHIFTC.MX2 (P1); also elsewhere on the board
ROW5: MOD4A.MX2 (P1), MOD4B.MX2 (P1), MOD5A.MX2 (P1), MOD5B.MX2 (P1), MOD5C.MX2 (P1), MOD6A.MX2 (P1), MOD6B.MX2 (P1), MOD7A.MX2 (P1), MOD7B.MX2 (P1), XTRA.MX2 (P1); also elsewhere on the board

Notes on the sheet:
Extra Key If Single 1U Backspace Key Is Used
Keyboard Matrix Right Half

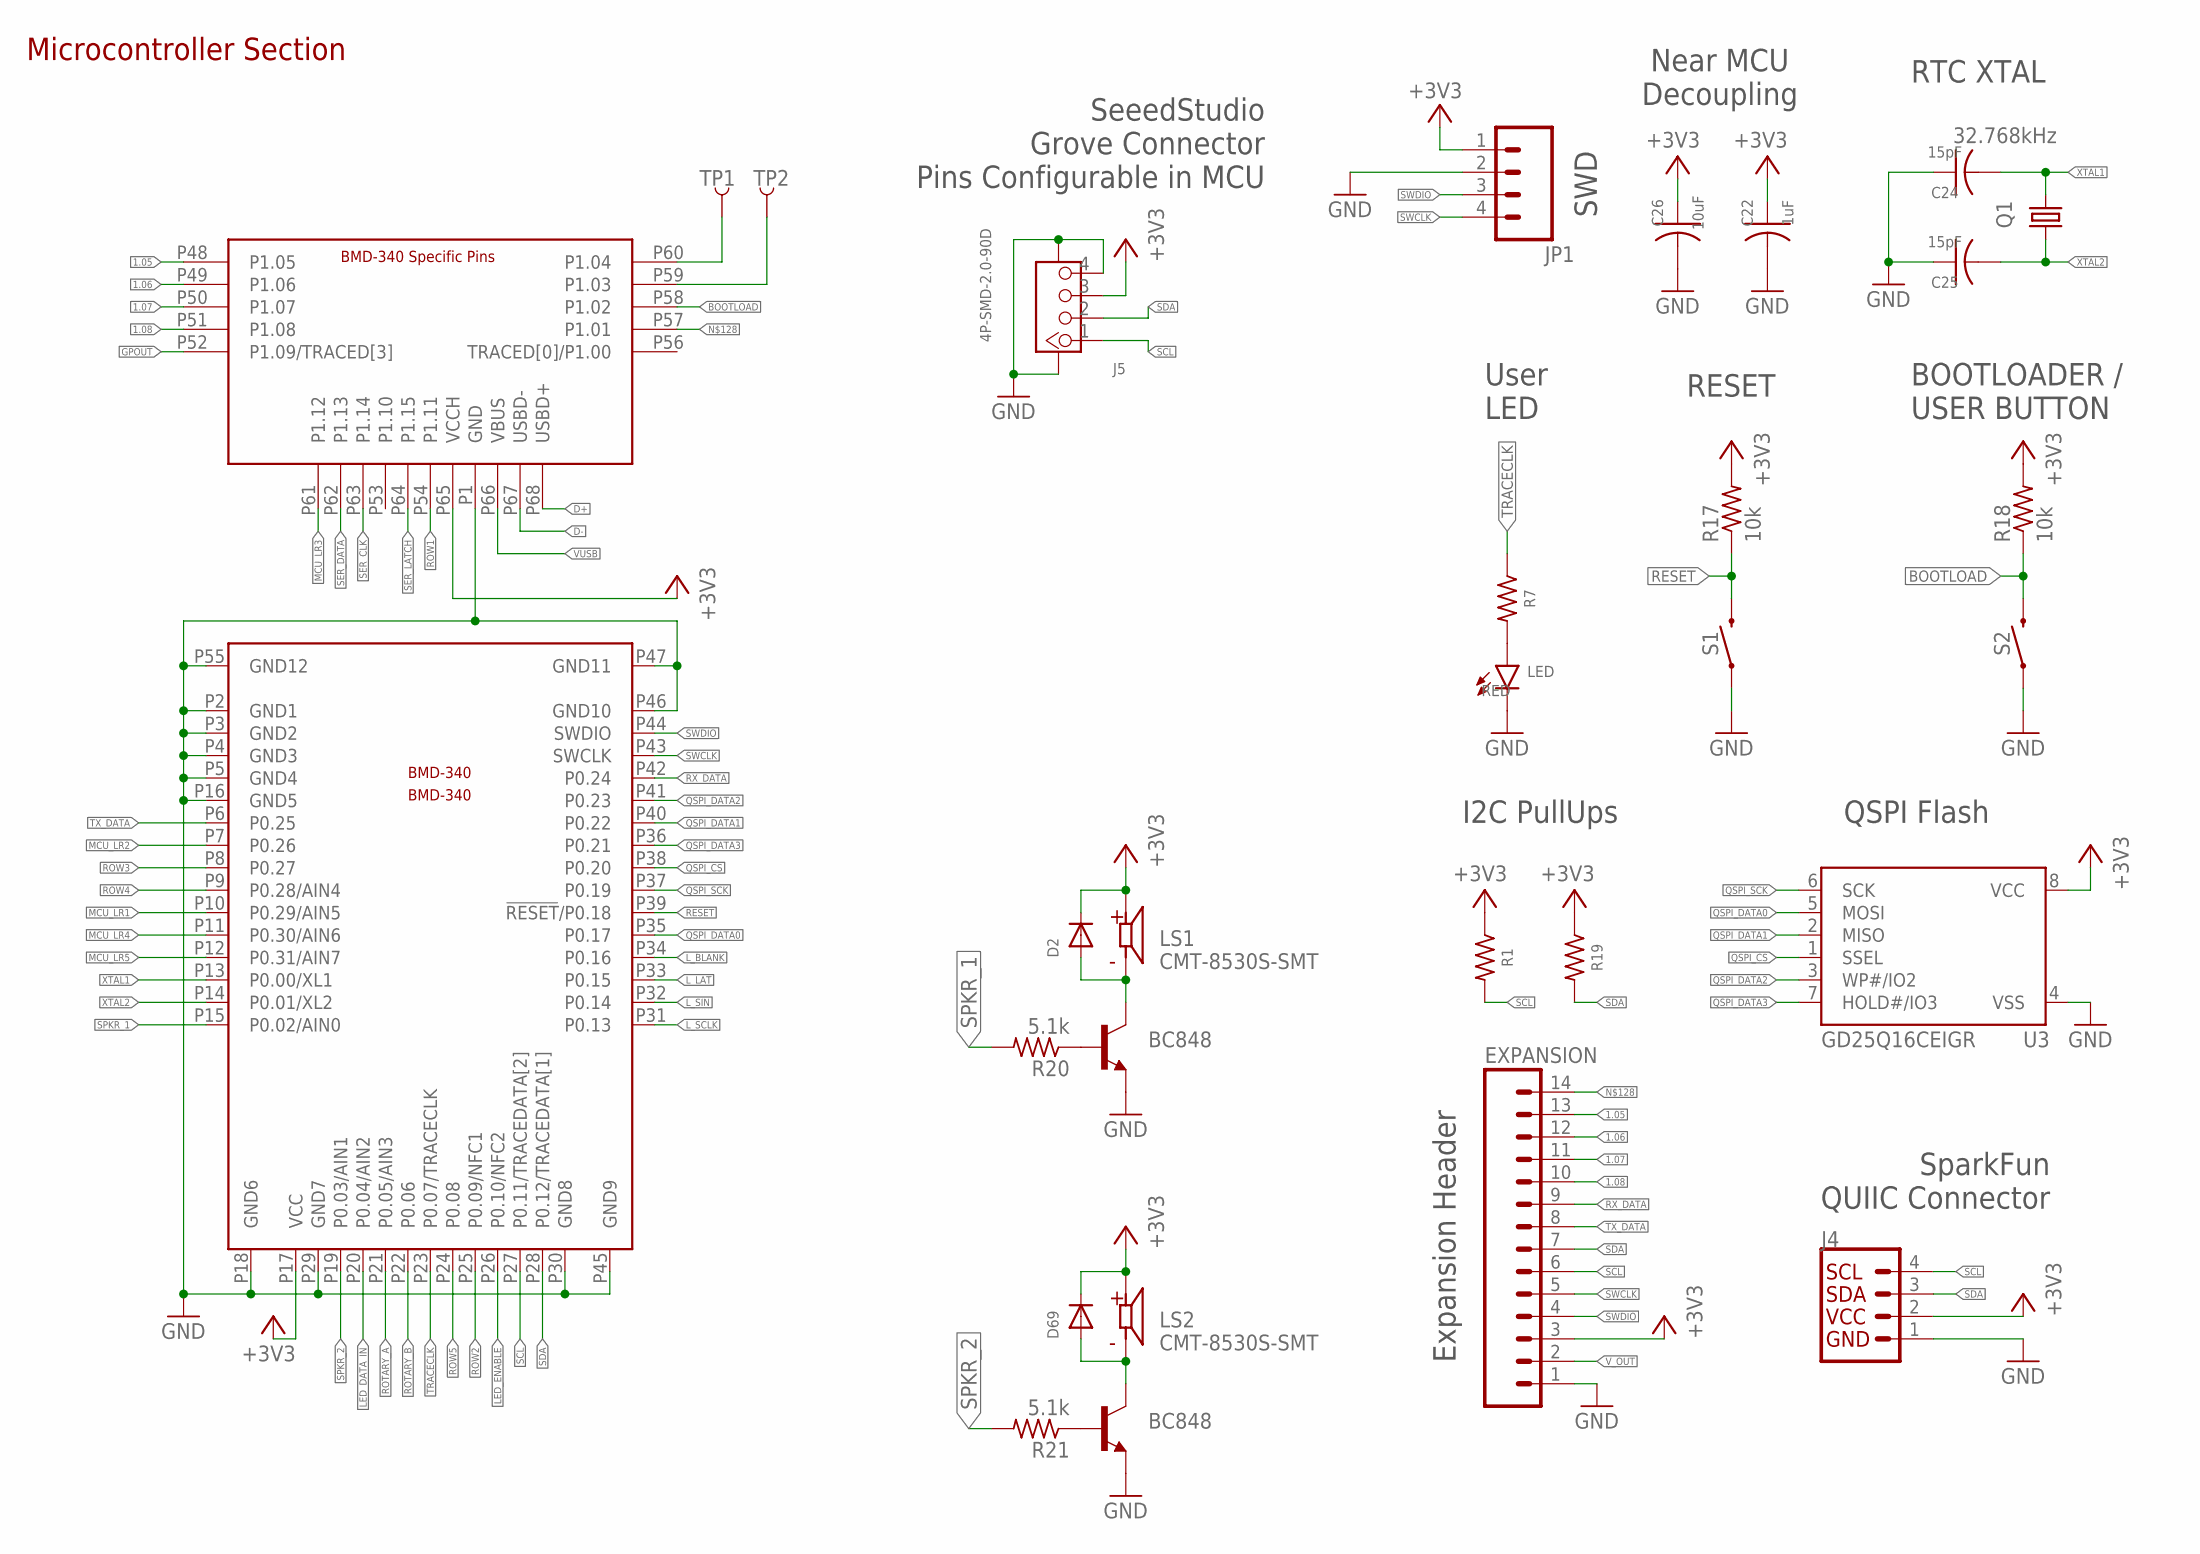
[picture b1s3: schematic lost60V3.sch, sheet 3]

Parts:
BMD-340: BMD-340
C22: 1uF; C0603K
C24, C25: 15pF; C0603K
C26: 10uF; C0603K
D2, D69: DIODESOD-523; SOD-523
EXPANSION: M14; 1X14
J4: QWIIC_CONNECTORJS-1MM; 1X04_1MM_RA
J5: 4P-SMD-2.0-90D; HW4-SMD-2.0-90D
JP1: M04PTH; 1X04
LED: RED; LED-0603
LS1, LS2: CMT-8530S-SMT; CUI_CMT-8530S-SMT
Q1: 32.768kHz; 3.2X1.5
R1, R7, R19: 1k; R0603
R17, R18: 10k; R0603
R20, R21: 5.1k; R0603
S1, S2: MOMENTARY-SWITCH-SPST-SMD-4.6X2.8MM; TACTILE_SWITCH_SMD_4.6X2.8MM
T6, T7: BC848; SOT23
TP1, TP2: TEST-POINT3X5; PAD.03X.05
U3: GD25Q16CEIGR; MICROBUILDER_USON8

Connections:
1.05: BMD-340.P48 (P1.05), EXPANSION.13
1.06: BMD-340.P49 (P1.06), EXPANSION.12
1.07: BMD-340.P50 (P1.07), EXPANSION.11
1.08: BMD-340.P51 (P1.08), EXPANSION.10
+3V1: D2.A, LS1.N, T6.3 (C)
+3V2: D69.A, LS2.N, T7.3 (C)
+3V3: BMD-340.P17 (VCC), BMD-340.P65 (VCCH), C22.1, C26.1, D2.K (C), D69.K (C), EXPANSION.3, J4.2 (VCC), J5.3, JP1.1, LS1.P, LS2.P, R1.1, R17.2, R18.2, R19.1, U3.8 (VCC); also elsewhere on the board
BOOTLOAD: BMD-340.P58 (P1.02), R18.1, S2.3 (2), S2.4 (2)
D+: BMD-340.P68 (USBD+); also elsewhere on the board
D-: BMD-340.P67 (USBD-); also elsewhere on the board
GND: BMD-340.P1 (GND), BMD-340.P2 (GND1), BMD-340.P3 (GND2), BMD-340.P4 (GND3), BMD-340.P5 (GND4), BMD-340.P16 (GND5), BMD-340.P18 (GND6), BMD-340.P29 (GND7), BMD-340.P30 (GND8), BMD-340.P45 (GND9), BMD-340.P46 (GND10), BMD-340.P47 (GND11), BMD-340.P55 (GND12), C22.2, C24.1, C25.1, C26.2, EXPANSION.1, J4.1 (GND), J5.4, J5.SS1, J5.SS2, JP1.2, LED.C, S1.1, S1.2 (1), S2.1, S2.2 (1), T6.2 (E), T7.2 (E), U3.4 (VSS); also elsewhere on the board
GPOUT: BMD-340.P52 (P1.09/TRACED[3]); also elsewhere on the board
LED_DATA_IN: BMD-340.P20 (P0.04/AIN2); also elsewhere on the board
LED_ENABLE: BMD-340.P26 (P0.10/NFC2); also elsewhere on the board
L_BLANK: BMD-340.P34 (P0.16); also elsewhere on the board
L_LAT: BMD-340.P33 (P0.15); also elsewhere on the board
L_SCLK: BMD-340.P31 (P0.13); also elsewhere on the board
L_SIN: BMD-340.P32 (P0.14); also elsewhere on the board
MCU_LR1: BMD-340.P10 (P0.29/AIN5); also elsewhere on the board
MCU_LR2: BMD-340.P7 (P0.26); also elsewhere on the board
MCU_LR3: BMD-340.P61 (P1.12); also elsewhere on the board
MCU_LR4: BMD-340.P11 (P0.30/AIN6); also elsewhere on the board
MCU_LR5: BMD-340.P12 (P0.31/AIN7); also elsewhere on the board
unnamed: LED.A, R7.2
unnamed: R20.1, T6.1 (B)
unnamed: R21.1, T7.1 (B)
unnamed: BMD-340.P57 (P1.01), EXPANSION.14
unnamed: BMD-340.P59 (P1.03), TP2.P$1
unnamed: BMD-340.P60 (P1.04), TP1.P$1
QSPI_CS: BMD-340.P38 (P0.20), U3.1 (SSEL)
QSPI_DATA0: BMD-340.P35 (P0.17), U3.5 (MOSI)
QSPI_DATA1: BMD-340.P40 (P0.22), U3.2 (MISO)
QSPI_DATA2: BMD-340.P41 (P0.23), U3.3 (WP#/IO2)
QSPI_DATA3: BMD-340.P36 (P0.21), U3.7 (HOLD#/IO3)
QSPI_SCK: BMD-340.P37 (P0.19), U3.6 (SCK)
RESET: BMD-340.P39 (!RESET!/P0.18), R17.1, S1.3 (2), S1.4 (2)
ROTARY_A: BMD-340.P21 (P0.05/AIN3); also elsewhere on the board
ROTARY_B: BMD-340.P22 (P0.06); also elsewhere on the board
ROW1: BMD-340.P54 (P1.11); also elsewhere on the board
ROW2: BMD-340.P25 (P0.09/NFC1); also elsewhere on the board
ROW3: BMD-340.P8 (P0.27); also elsewhere on the board
ROW4: BMD-340.P9 (P0.28/AIN4); also elsewhere on the board
ROW5: BMD-340.P24 (P0.08); also elsewhere on the board
RX_DATA: BMD-340.P42 (P0.24), EXPANSION.9
SCL: BMD-340.P27 (P0.11/TRACEDATA[2]), EXPANSION.6, J4.4 (SCL), J5.1, R1.2; also elsewhere on the board
SDA: BMD-340.P28 (P0.12/TRACEDATA[1]), EXPANSION.7, J4.3 (SDA), J5.2, R19.2; also elsewhere on the board
SER_CLK: BMD-340.P63 (P1.14); also elsewhere on the board
SER_DATA: BMD-340.P62 (P1.13); also elsewhere on the board
SER_LATCH: BMD-340.P64 (P1.15); also elsewhere on the board
SPKR_1: BMD-340.P15 (P0.02/AIN0), R20.2
SPKR_2: BMD-340.P19 (P0.03/AIN1), R21.2
SWCLK: BMD-340.P43 (SWCLK), EXPANSION.5, JP1.4
SWDIO: BMD-340.P44 (SWDIO), EXPANSION.4, JP1.3
TRACECLK: BMD-340.P23 (P0.07/TRACECLK), R7.1
TX_DATA: BMD-340.P6 (P0.25), EXPANSION.8
VUSB: BMD-340.P66 (VBUS); also elsewhere on the board
V_OUT: EXPANSION.2; also elsewhere on the board
XTAL1: BMD-340.P13 (P0.00/XL1), C24.2, Q1.2
XTAL2: BMD-340.P14 (P0.01/XL2), C25.2, Q1.1

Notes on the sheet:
SWD
Microcontroller Section
Near MCU Decoupling
RTC XTAL
User LED
RESET
BOOTLOADER / USER BUTTON
I2C PullUps
QSPI Flash
SparkFun QUIIC Connector
Expansion Header
SeeedStudio Grove Connector Pins Configurable in MCU

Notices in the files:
parts and their libraries:
SparkFun-Connectors: Licensing: Creative Commons ShareAlike 4.0 International - https://creativecommons.org/licenses/by-sa/4.0
